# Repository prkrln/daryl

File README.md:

Portable 32 key unibody. My mom named it Daryl <3.

Firmware:
https://github.com/prkrln/qmk_firmware

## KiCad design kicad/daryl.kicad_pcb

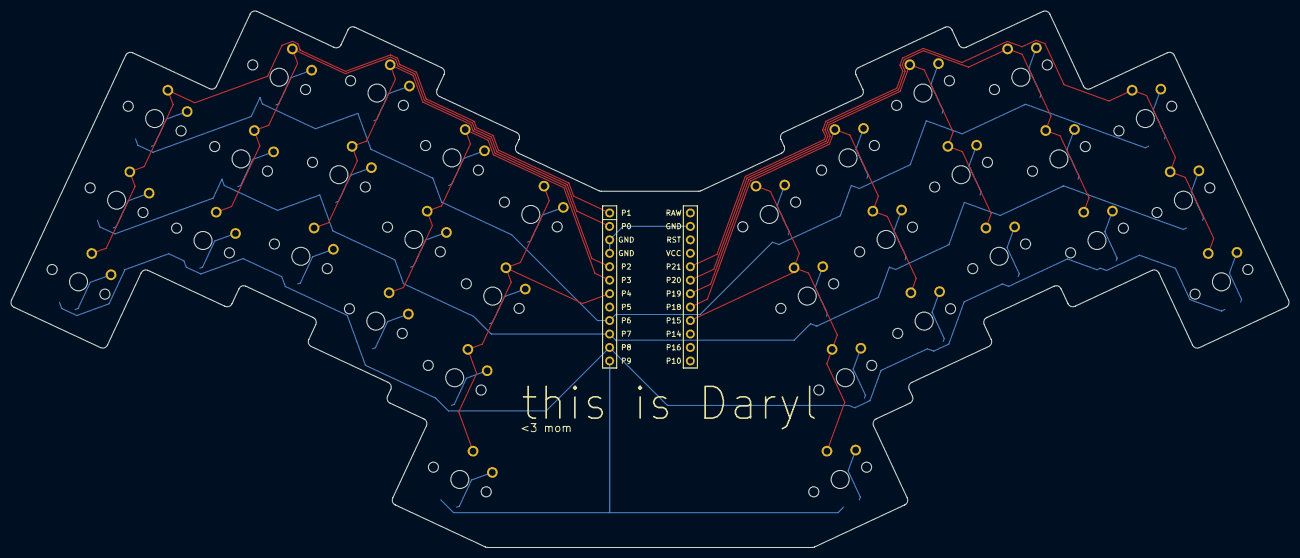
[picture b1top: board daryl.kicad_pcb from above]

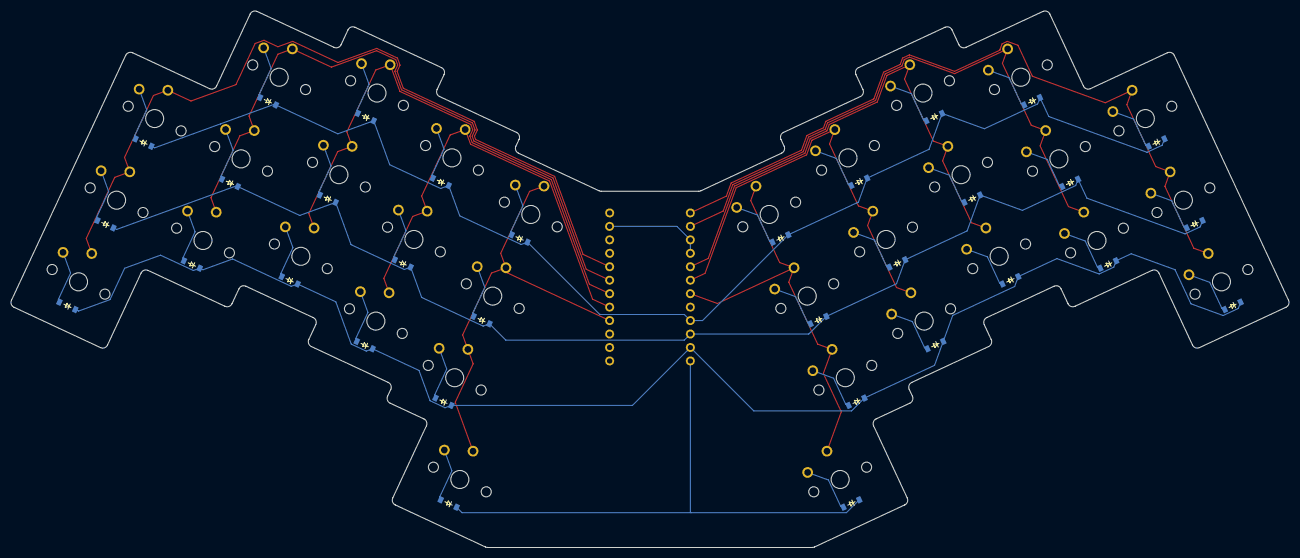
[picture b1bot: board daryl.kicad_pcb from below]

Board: 2 copper layers, 241.2 x 101.3 mm, 65 parts (64 on the bottom side), 47 nets.

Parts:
D1, D2, D3, D4, D5, D6, D7, D8, D9, D10, D11, D12, D13, D14, D15, D16, D17, D18, D19, D20, D21, D22, D23, D24, D25, D26, D27, D28, D29, D30, D31, D32: diode_tht_sod123
MCU1: mcu_nice_nano
S1, S2, S3, S4, S5, S6, S7, S8, S9, S10, S11, S12, S13, S14, S15, S16, S17, S18, S19, S20, S21, S22, S23, S24, S25, S26, S27, S28, S29, S30, S31, S32: switch_choc_v1_v2

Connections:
GND: MCU1.2, MCU1.21, MCU1.22
P0: MCU1.23, S4.2, S5.2, S6.2
P1: MCU1.24, S1.2, S2.2, S3.2
P2: MCU1.20, S7.2, S8.2, S9.2
P3: MCU1.19, S10.2, S11.2, S12.2
P4: MCU1.18, S13.2, S14.2, S15.2, S16.2
P6: D3.1, D6.1, D9.1, D12.1, D15.1, D19.1, D22.1, D25.1, D28.1, D31.1, MCU1.16
P7: D2.1, D5.1, D8.1, D11.1, D14.1, D18.1, D21.1, D24.1, D27.1, D30.1, MCU1.15
P8: D1.1, D4.1, D7.1, D10.1, D13.1, D17.1, D20.1, D23.1, D26.1, D29.1, MCU1.14
P9: D16.1, D32.1, MCU1.13
P15: MCU1.9, S29.2, S30.2, S31.2, S32.2
P18: MCU1.8, S26.2, S27.2, S28.2
P19: MCU1.7, S23.2, S24.2, S25.2
P20: MCU1.6, S20.2, S21.2, S22.2
P21: MCU1.5, S17.2, S18.2, S19.2
column_row: D16.2, S16.1
index_bottom: D10.2, S10.1
index_home: D11.2, S11.1
index_top: D12.2, S12.1
inner_bottom: D13.2, S13.1
inner_home: D14.2, S14.1
inner_top: D15.2, S15.1
middle_bottom: D7.2, S7.1
middle_home: D8.2, S8.1
middle_top: D9.2, S9.1
mirror_column_row: D32.2, S32.1
mirror_index_bottom: D26.2, S26.1
mirror_index_home: D27.2, S27.1
mirror_index_top: D28.2, S28.1
mirror_inner_bottom: D29.2, S29.1
mirror_inner_home: D30.2, S30.1
mirror_inner_top: D31.2, S31.1
mirror_middle_bottom: D23.2, S23.1
mirror_middle_home: D24.2, S24.1
mirror_middle_top: D25.2, S25.1
mirror_pinky_bottom: D17.2, S17.1
mirror_pinky_home: D18.2, S18.1
mirror_pinky_top: D19.2, S19.1
mirror_ring_bottom: D20.2, S20.1
mirror_ring_home: D21.2, S21.1
mirror_ring_top: D22.2, S22.1
pinky_bottom: D1.2, S1.1
pinky_home: D2.2, S2.1
pinky_top: D3.2, S3.1
ring_bottom: D4.2, S4.1
ring_home: D5.2, S5.1
ring_top: D6.2, S6.1

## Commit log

2025-12-30 Add README with keyboard image and description
2026-01-06 Update firmware link in README
